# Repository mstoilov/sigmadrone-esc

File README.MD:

This is the sigmadrone ESC repository. It contains hardware designs and
firmware software for the Sigmadrone ESC.

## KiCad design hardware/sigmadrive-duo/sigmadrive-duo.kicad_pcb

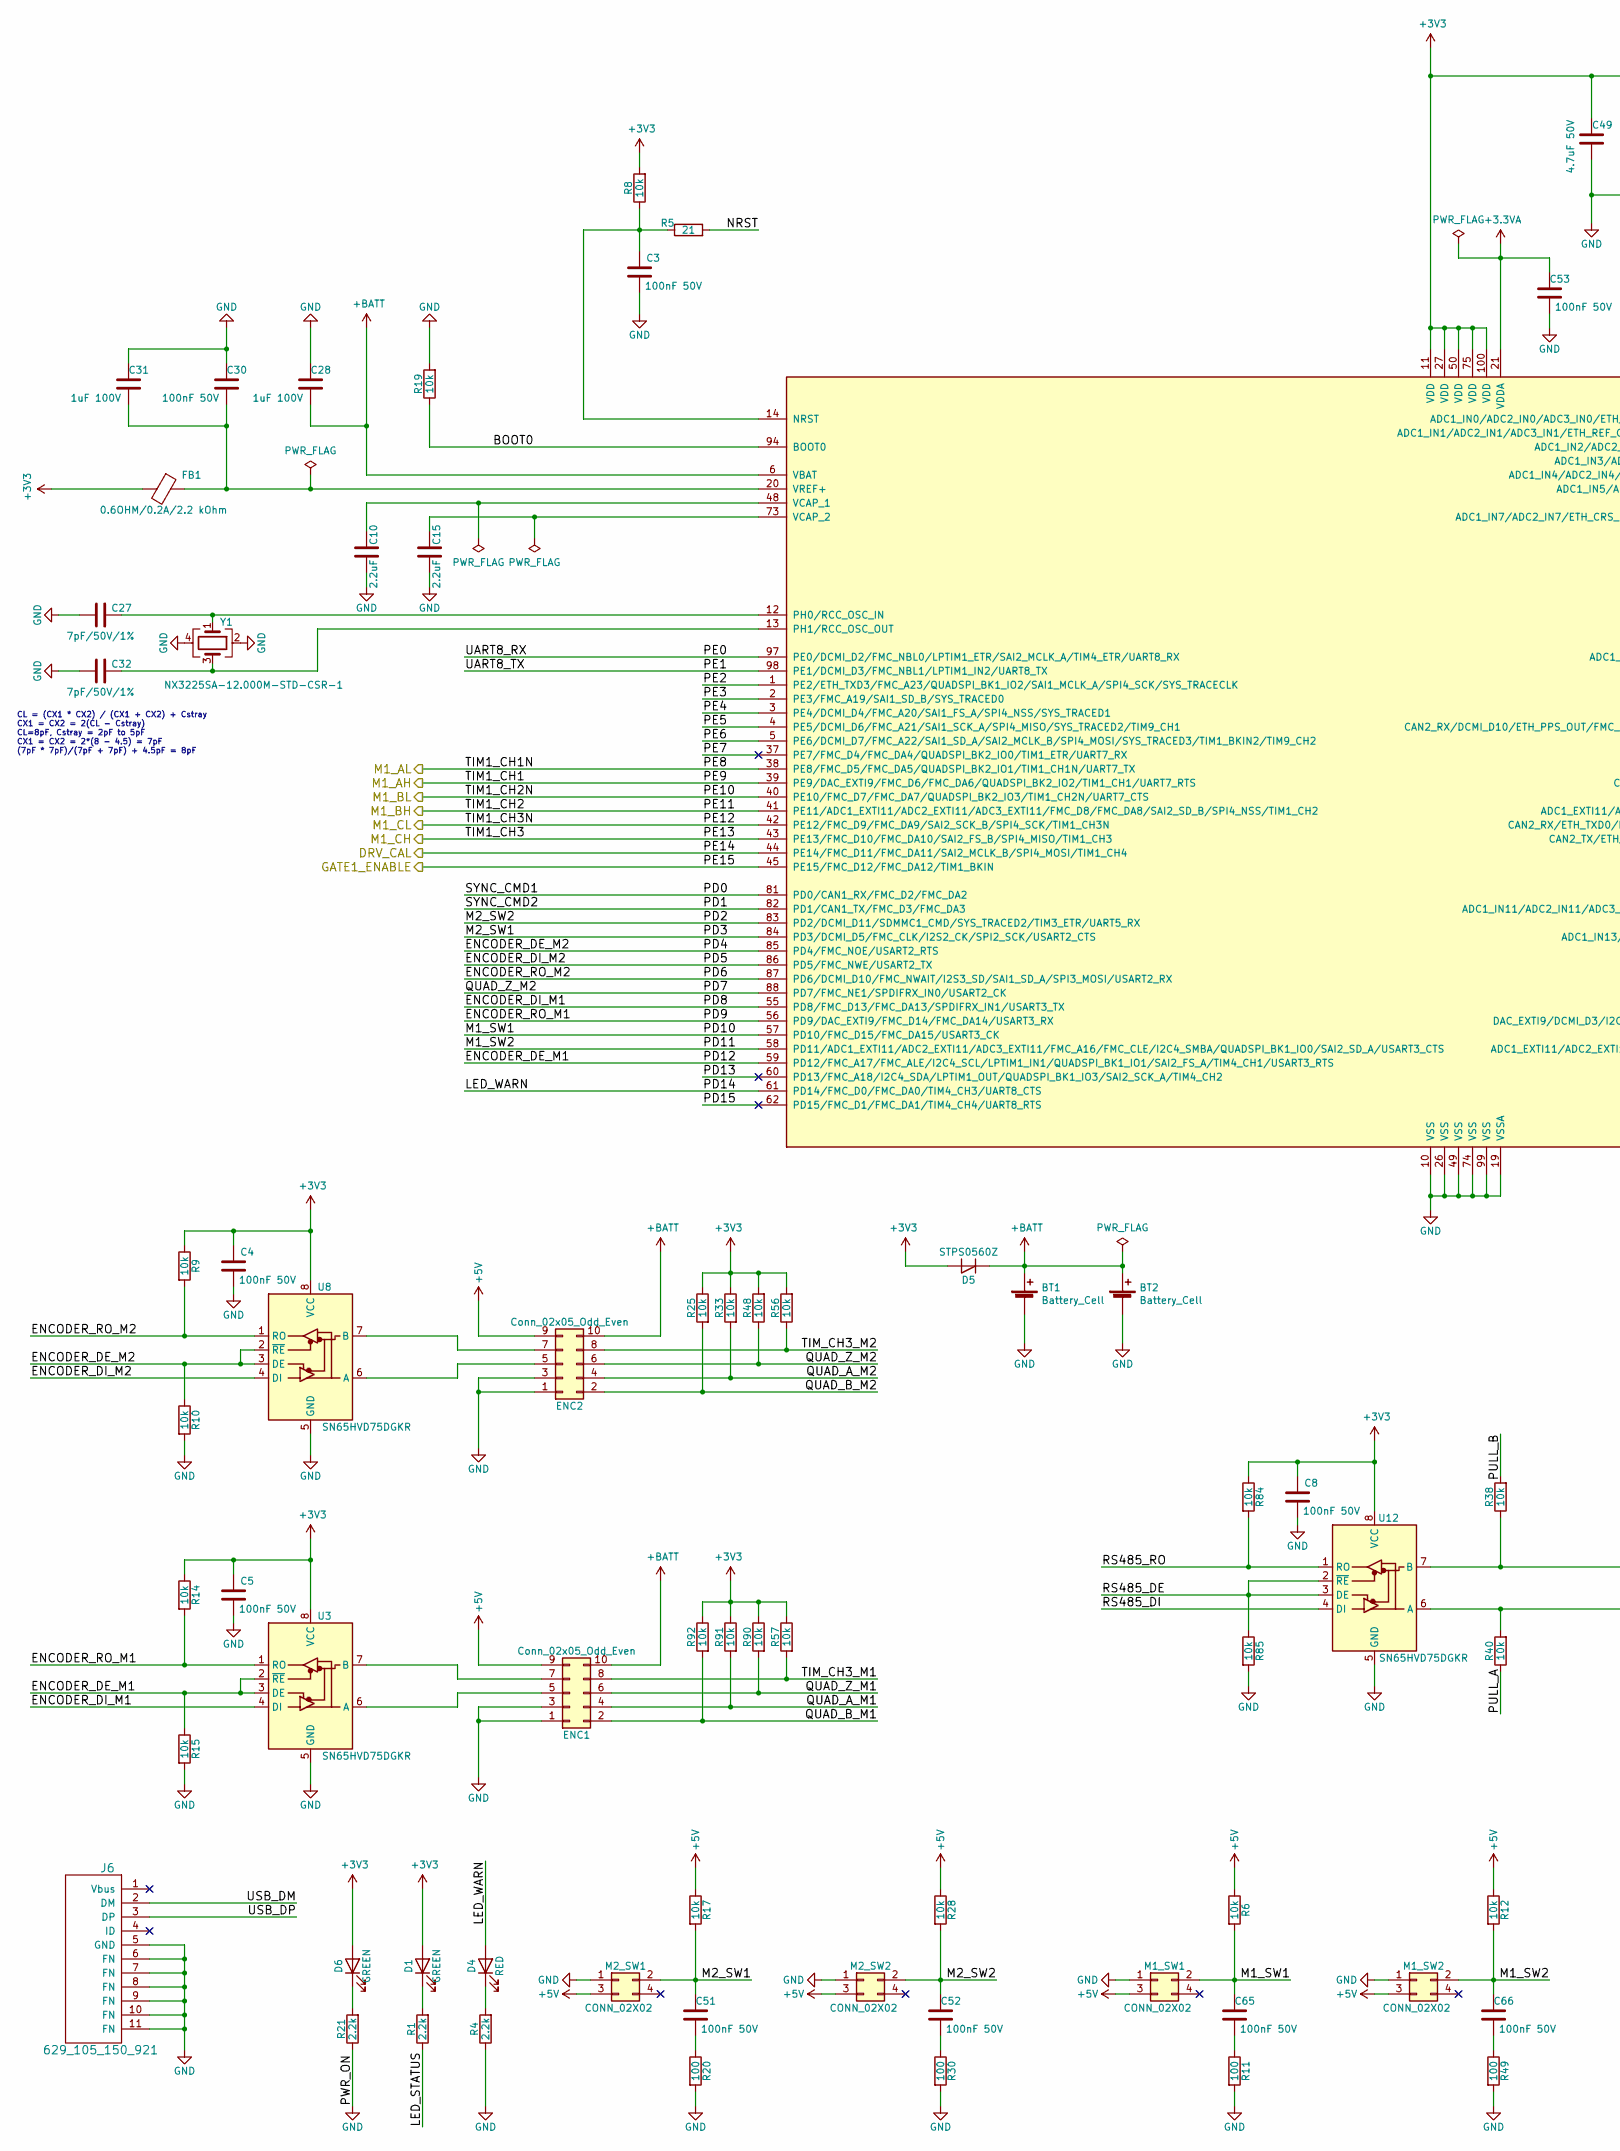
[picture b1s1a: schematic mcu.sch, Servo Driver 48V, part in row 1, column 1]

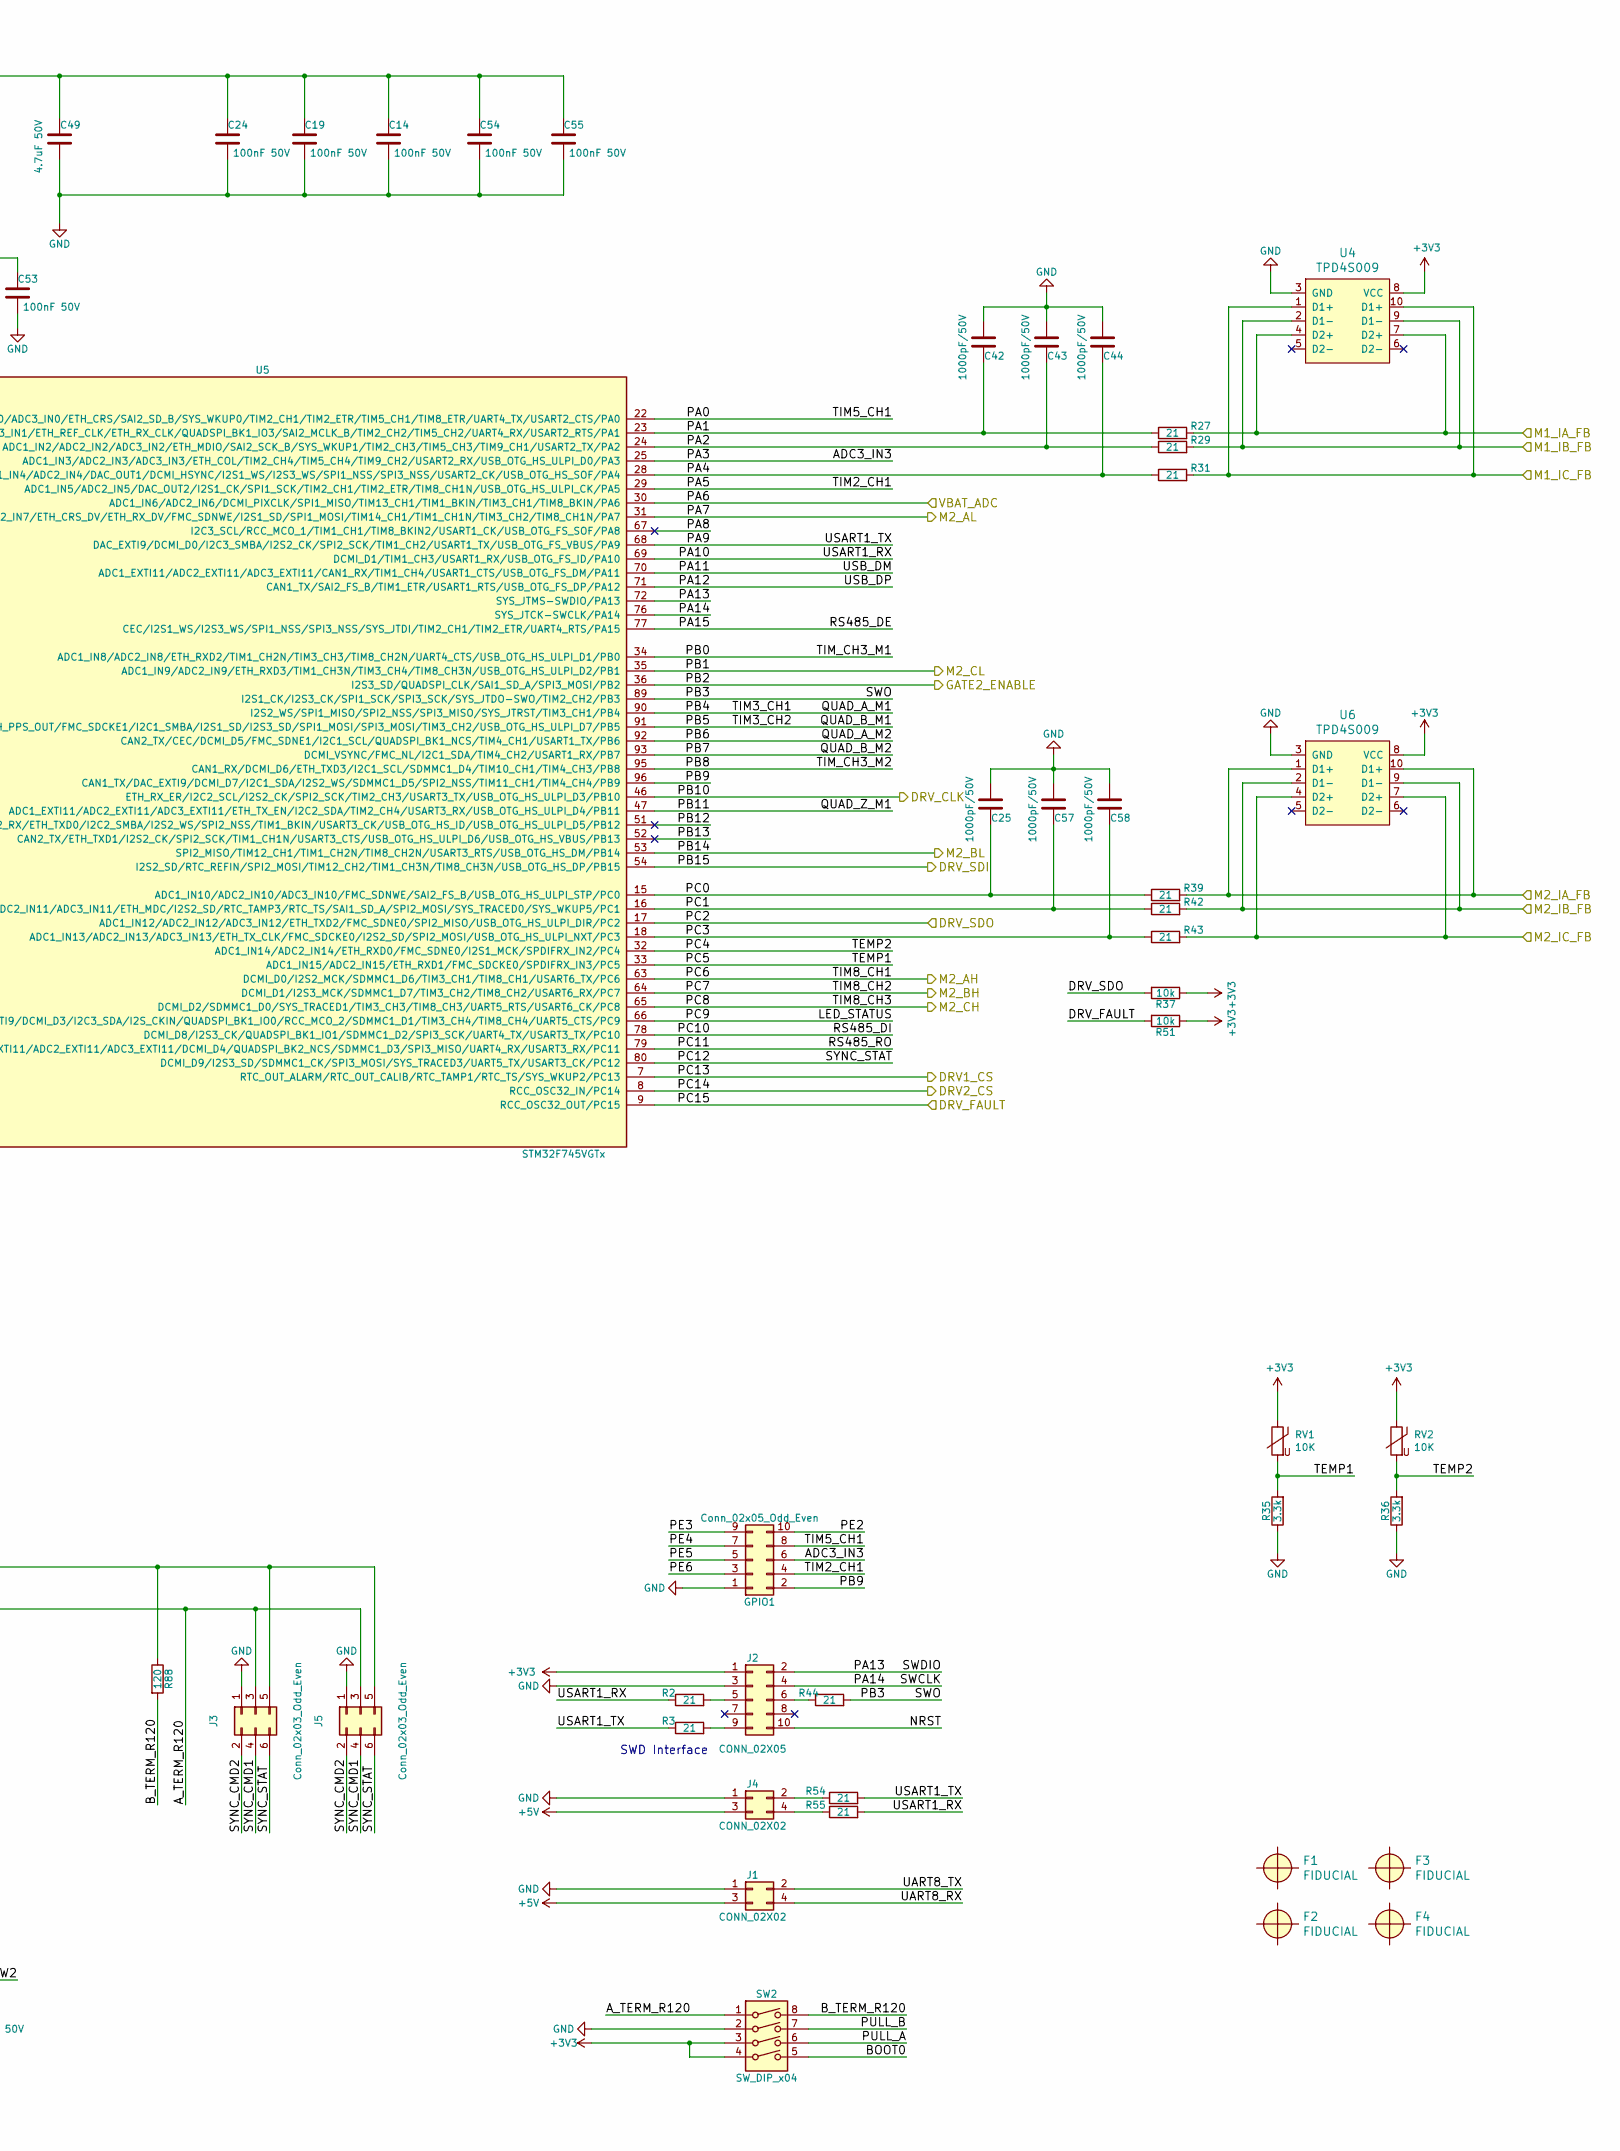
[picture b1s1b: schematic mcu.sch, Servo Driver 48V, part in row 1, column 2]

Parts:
BT1, BT2: Battery_Cell; Battery_Panasonic_CR1220-VCN_Vertical_CircularHoles; Part VL-1220/VCN
C3, C4, C5, C8, C14, C19, C24, C30, C51, C52, C53, C54, C55, C65, C66: 100nF 50V; C_0603_1608Metric; Part 490-4779-2-ND
C10, C15: 2.2uF; C_0603_1608Metric; Part 490-10731-1-ND
C25, C42, C43, C44, C57, C58: 1000pF/50V; C_0603_1608Metric; Part 1276-1091-2-ND
C27, C32: 7pF/50V/1%; C_0603_1608Metric; Part ‎1276-2137-1-ND‎
C28, C31: 1uF 100V; C_0805_2012Metric; Part 445-6804-2-ND
C49: 4.7uF 50V; C_0805_2012Metric; Part 490-10751-2-ND
D1, D6: GREEN; LED_0603_1608Metric; Part 732-4971-1-ND
D4: RED; LED_0603_1608Metric; Part 732-4978-1-ND
D5: STPS0560Z; D_SOD-123; Part 497-3787-1-ND
ENC1, ENC2: Conn_02x05_Odd_Even; PinHeader_2x05_P2.00mm_Horizontal; Part H10247-ND
F1, F2, F3, F4: FIDUCIAL; Fiducial_0.5mm_Dia_1mm_Outer
FB1: 0.6OHM/0.2A/2.2 kOhm; R_0603_1608Metric; Part 732-1609-1-ND
GPIO1: Conn_02x05_Odd_Even; PinHeader_2x05_P2.00mm_Horizontal
J1, J4: CONN_02X02; PinHeader_2x02_P2.00mm_Horizontal; Part 732-5374-ND
J2: CONN_02X05; PinHeader_2x05_P1.27mm_Vertical; Part 732-5374-ND
J3, J5: Conn_02x03_Odd_Even; PinHeader_2x03_P2.00mm_Horizontal; Part H2866-ND
J6: 629_105_150_921; WURTH_629105150921_NO_OVALS; Part 732-5961-1-ND
M1_SW1, M1_SW2, M2_SW1, M2_SW2: CONN_02X02; PinHeader_2x02_P2.00mm_Horizontal; Part H10244-ND
R1, R4, R21: 2.2k; R_0603_1608Metric; Part RMCF0603JT2K20CT-ND
R2, R3, R5, R27, R29, R31, R39, R42, R43, R44, R54, R55: 21; R_0603_1608Metric; Part 311-21.0HRCT-ND
R6, R8, R9, R10, R12, R14, R15, R17, R19, R25, R28, R33, R37, R38, R40, R48, R51, R56, R57, R84, R85, R90, R91, R92: 10k; R_0603_1608Metric; Part 311-10.0KHRCT-ND
R11, R20, R30, R49: 100; R_0603_1608Metric; Part 311-100HRCT-ND
R35, R36: 3.3k; R_0603_1608Metric; Part 311-3.30KHRCT-ND
R88: 120; R_0603_1608Metric; Part 311-100HRCT-ND
RV1, RV2: 10K; R_0603_1608Metric; Part P12014CT-ND
SW2: SW_DIP_x04; SW_DIP_SPSTx04_Slide_Copal_CHS-04A_W5.08mm_P1.27mm_JPin; Part GH7644CT-ND
U3, U8, U12: SN65HVD75DGKR; SOIC-8_3.9x4.9mm_P1.27mm; Part 296-35070-1-ND
U4, U6: TPD4S009; TSSOP-10_3x3mm_P0.5mm; Part 296-24538-1-ND
U5: STM32F745VGTx; LQFP-100_14x14mm_P0.5mm; Part 497-16605-ND
Y1: NX3225SA-12.000M-STD-CSR-1; Crystal_SMD_3225-4Pin_3.2x2.5mm; Part 644-1047-1-ND

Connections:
+3.3VA: C53.2, U5.21 (VDDA); also elsewhere on the board
+5V: ENC1.9, ENC2.9, J1.3, J4.3, M1_SW1.3, M1_SW2.3, M2_SW1.3, M2_SW2.3, R6.1, R12.1, R17.1, R28.1; also elsewhere on the board
+BATT: BT1.1 (+), BT2.1 (+), C28.1, D5.1 (K), ENC1.10, ENC2.10, U5.6 (VBAT)
/MCU/ADC3_IN3: GPIO1.6, U5.25 (ADC1_IN3/ADC2_IN3/ADC3_IN3/ETH_COL/TIM2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)
/MCU/A_TERM_R120: J3.3, J5.3, R40.2, SW2.1, U12.6 (A)
/MCU/BOOT0: R19.1, SW2.5, U5.94 (BOOT0)
/MCU/B_TERM_R120: R88.2, SW2.8
/MCU/DRV1_CS: U5.7 (RTC_OUT_ALARM/RTC_OUT_CALIB/RTC_TAMP1/R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); also elsewhere on the board
/MCU/DRV2_CS: U5.8 (RCC_OSC32_IN/PC14); also elsewhere on the board
/MCU/DRV_CAL: U5.44 (PE14/FMC_D11/FMC_DA11/SAI2_MCLK_B/SPI4_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); also elsewhere on the board
/MCU/DRV_CLK: U5.46 (ETH_RX_ER/I2C2_SCL/I2S2_CK/SPI2_SCK/TIM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); also elsewhere on the board
/MCU/DRV_FAULT: R51.2, U5.9 (RCC_OSC32_OUT/PC15); also elsewhere on the board
/MCU/DRV_SDI: U5.54 (I2S2_SD/RTC_REFIN/SPI2_MOSI/TIM12_CH2/T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); also elsewhere on the board
/MCU/DRV_SDO: R37.2, U5.17 (ADC1_IN12/ADC2_IN12/ADC3_IN12/ETH_TXD2/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); also elsewhere on the board
/MCU/ENCODER_DE_M1: R15.1, U3.2 (~RE), U3.3 (DE), U5.59 (PD12/FMC_A17/FMC_ALE/I2C4_SCL/LPTIM1_IN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)
/MCU/ENCODER_DE_M2: R10.1, U5.85 (PD4/FMC_NOE/USART2_RTS), U8.2 (~RE), U8.3 (DE)
/MCU/ENCODER_DI_M1: U3.4 (DI), U5.55 (PD8/FMC_D13/FMC_DA13/SPDIFRX_IN1/USART3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)
/MCU/ENCODER_DI_M2: U5.86 (PD5/FMC_NWE/USART2_TX), U8.4 (DI)
/MCU/ENCODER_RO_M1: R14.2, U3.1 (RO), U5.56 (PD9/DAC_EXTI9/FMC_D14/FMC_DA14/USART3_RX)
/MCU/ENCODER_RO_M2: R9.2, U5.87 (PD6/DCMI_D10/FMC_NWAIT/I2S3_SD/SAI1_SD_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), U8.1 (RO)
/MCU/GATE1_ENABLE: U5.45 (PE15/FMC_D12/FMC_DA12/TIM1_BKIN); also elsewhere on the board
/MCU/GATE2_ENABLE: U5.36 (I2S3_SD/QUADSPI_CLK/SAI1_SD_A/SPI3_MOSI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); also elsewhere on the board
/MCU/LED_STATUS: R1.1, U5.66 (DAC_EXTI9/DCMI_D3/I2C3_SDA/I2S_CKIN/QUA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)
/MCU/LED_WARN: D4.2 (A), U5.61 (PD14/FMC_D0/FMC_DA0/TIM4_CH3/UART8_CTS)
/MCU/M1_AH: U5.39 (PE9/DAC_EXTI9/FMC_D6/FMC_DA6/QUADSPI_BK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); also elsewhere on the board
/MCU/M1_AL: U5.38 (PE8/FMC_D5/FMC_DA5/QUADSPI_BK2_IO1/TIM1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); also elsewhere on the board
/MCU/M1_BH: U5.41 (PE11/ADC1_EXTI11/ADC2_EXTI11/ADC3_EXTI1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); also elsewhere on the board
/MCU/M1_BL: U5.40 (PE10/FMC_D7/FMC_DA7/QUADSPI_BK2_IO3/TIM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); also elsewhere on the board
/MCU/M1_CH: U5.43 (PE13/FMC_D10/FMC_DA10/SAI2_FS_B/SPI4_MI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); also elsewhere on the board
/MCU/M1_CL: U5.42 (PE12/FMC_D9/FMC_DA9/SAI2_SCK_B/SPI4_SCK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); also elsewhere on the board
/MCU/M1_IA_FB: R27.2, U4.4 (D2+), U4.7 (D2+); also elsewhere on the board
/MCU/M1_IB_FB: R29.2, U4.2 (D1-), U4.9 (D1-); also elsewhere on the board
/MCU/M1_IC_FB: R31.2, U4.1 (D1+), U4.10 (D1+); also elsewhere on the board
/MCU/M1_SW1: C65.2, M1_SW1.2, R6.2, U5.57 (PD10/FMC_D15/FMC_DA15/USART3_CK)
/MCU/M1_SW2: C66.2, M1_SW2.2, R12.2, U5.58 (PD11/ADC1_EXTI11/ADC2_EXTI11/ADC3_EXTI1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)
/MCU/M2_AH: U5.63 (DCMI_D0/I2S2_MCK/SDMMC1_D6/TIM3_CH1/TIM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); also elsewhere on the board
/MCU/M2_AL: U5.31 (ADC1_IN7/ADC2_IN7/ETH_CRS_DV/ETH_RX_DV/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); also elsewhere on the board
/MCU/M2_BH: U5.64 (DCMI_D1/I2S3_MCK/SDMMC1_D7/TIM3_CH2/TIM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); also elsewhere on the board
/MCU/M2_BL: U5.53 (SPI2_MISO/TIM12_CH1/TIM1_CH2N/TIM8_CH2N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); also elsewhere on the board
/MCU/M2_CH: U5.65 (DCMI_D2/SDMMC1_D0/SYS_TRACED1/TIM3_CH3/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); also elsewhere on the board
/MCU/M2_CL: U5.35 (ADC1_IN9/ADC2_IN9/ETH_RXD3/TIM1_CH3N/TI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); also elsewhere on the board
/MCU/M2_IA_FB: R39.2, U6.1 (D1+), U6.10 (D1+); also elsewhere on the board
/MCU/M2_IB_FB: R42.2, U6.2 (D1-), U6.9 (D1-); also elsewhere on the board
/MCU/M2_IC_FB: R43.2, U6.4 (D2+), U6.7 (D2+); also elsewhere on the board
/MCU/M2_SW1: C51.2, M2_SW1.2, R17.2, U5.84 (PD3/DCMI_D5/FMC_CLK/I2S2_CK/SPI2_SCK/US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)
/MCU/M2_SW2: C52.2, M2_SW2.2, R28.2, U5.83 (PD2/DCMI_D11/SDMMC1_CMD/SYS_TRACED2/TIM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)
/MCU/NRST: J2.10, R5.2
/MCU/PA0: GPIO1.8, U5.22 (ADC1_IN0/ADC2_IN0/ADC3_IN0/ETH_CRS/SAI2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)
/MCU/PA1: C42.1, R27.1, U5.23 (ADC1_IN1/ADC2_IN1/ADC3_IN1/ETH_REF_CLK/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)
/MCU/PA2: C43.1, R29.1, U5.24 (ADC1_IN2/ADC2_IN2/ADC3_IN2/ETH_MDIO/SAI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)
/MCU/PA4: C44.1, R31.1, U5.28 (ADC1_IN4/ADC2_IN4/DAC_OUT1/DCMI_HSYNC/I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)
/MCU/PA5: GPIO1.4, U5.29 (ADC1_IN5/ADC2_IN5/DAC_OUT2/I2S1_CK/SPI1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)
/MCU/PA8: U5.67 (I2C3_SCL/RCC_MCO_1/TIM1_CH1/TIM8_BKIN2/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)
/MCU/PA9: R3.1, R54.2, U5.68 (DAC_EXTI9/DCMI_D0/I2C3_SMBA/I2S2_CK/SPI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)
/MCU/PA10: R2.1, R55.2, U5.69 (DCMI_D1/TIM1_CH3/USART1_RX/USB_OTG_FS_I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)
/MCU/PA11: J6.2 (DM), U5.70 (ADC1_EXTI11/ADC2_EXTI11/ADC3_EXTI11/CAN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)
/MCU/PA12: J6.3 (DP), U5.71 (CAN1_TX/SAI2_FS_B/TIM1_ETR/USART1_RTS/U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)
/MCU/PA13: J2.2, U5.72 (SYS_JTMS-SWDIO/PA13)
/MCU/PA14: J2.4, U5.76 (SYS_JTCK-SWCLK/PA14)
/MCU/PA15: R85.1, U5.77 (CEC/I2S1_WS/I2S3_WS/SPI1_NSS/SPI3_NSS/S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), U12.2 (~RE), U12.3 (DE)
/MCU/PB0: ENC1.8, R57.2, U5.34 (ADC1_IN8/ADC2_IN8/ETH_RXD2/TIM1_CH2N/TI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)
/MCU/PB3: R44.2, U5.89 (I2S1_CK/I2S3_CK/SPI1_SCK/SPI3_SCK/SYS_J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)
/MCU/PB4: ENC1.4, R91.2, U5.90 (I2S2_WS/SPI1_MISO/SPI2_NSS/SPI3_MISO/SY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)
/MCU/PB5: ENC1.2, R92.2, U5.91 (CAN2_RX/DCMI_D10/ETH_PPS_OUT/FMC_SDCKE1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)
/MCU/PB6: ENC2.4, R33.2, U5.92 (CAN2_TX/CEC/DCMI_D5/FMC_SDNE1/I2C1_SCL/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)
/MCU/PB7: ENC2.2, R25.2, U5.93 (DCMI_VSYNC/FMC_NL/I2C1_SDA/TIM4_CH2/USA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)
/MCU/PB8: ENC2.8, R56.1, U5.95 (CAN1_RX/DCMI_D6/ETH_TXD3/I2C1_SCL/SDMMC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)
/MCU/PB9: GPIO1.2, U5.96 (CAN1_TX/DAC_EXTI9/DCMI_D7/I2C1_SDA/I2S2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)
/MCU/PB11: ENC1.6, R90.2, U5.47 (ADC1_EXTI11/ADC2_EXTI11/ADC3_EXTI11/ETH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)
/MCU/PB12: U5.51 (CAN2_RX/ETH_TXD0/I2C2_SMBA/I2S2_WS/SPI2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)
/MCU/PB13: U5.52 (CAN2_TX/ETH_TXD1/I2S2_CK/SPI2_SCK/TIM1_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)
/MCU/PC0: C25.1, R39.1, U5.15 (ADC1_IN10/ADC2_IN10/ADC3_IN10/FMC_SDNWE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)
/MCU/PC1: C57.1, R42.1, U5.16 (ADC1_IN11/ADC2_IN11/ADC3_IN11/ETH_MDC/I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)
/MCU/PC3: C58.1, R43.1, U5.18 (ADC1_IN13/ADC2_IN13/ADC3_IN13/ETH_TX_CL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)
/MCU/PC4: R36.2, RV2.2, U5.32 (ADC1_IN14/ADC2_IN14/ETH_RXD0/FMC_SDNE0/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)
/MCU/PC5: R35.2, RV1.2, U5.33 (ADC1_IN15/ADC2_IN15/ETH_RXD1/FMC_SDCKE0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)
/MCU/PC10: U5.78 (DCMI_D8/I2S3_CK/QUADSPI_BK1_IO1/SDMMC1_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), U12.4 (DI)
/MCU/PC11: R84.2, U5.79 (ADC1_EXTI11/ADC2_EXTI11/ADC3_EXTI11/DCM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), U12.1 (RO)
/MCU/PC12: J3.6, J5.6, U5.80 (DCMI_D9/I2S3_SD/SDMMC1_CK/SPI3_MOSI/SYS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)
/MCU/PD0: J3.4, J5.4, U5.81 (PD0/CAN1_RX/FMC_D2/FMC_DA2)
/MCU/PD1: J3.2, J5.2, U5.82 (PD1/CAN1_TX/FMC_D3/FMC_DA3)
/MCU/PD7: ENC2.6, R48.1, U5.88 (PD7/FMC_NE1/SPDIFRX_IN0/USART2_CK)
/MCU/PD13: U5.60 (PD13/FMC_A18/I2C4_SDA/LPTIM1_OUT/QUADSP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)
/MCU/PD15: U5.62 (PD15/FMC_D1/FMC_DA1/TIM4_CH4/UART8_RTS)
/MCU/PE0: J1.4, U5.97 (PE0/DCMI_D2/FMC_NBL0/LPTIM1_ETR/SAI2_MC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)
/MCU/PE1: J1.2, U5.98 (PE1/DCMI_D3/FMC_NBL1/LPTIM1_IN2/UART8_TX)
/MCU/PE2: GPIO1.10, U5.1 (PE2/ETH_TXD3/FMC_A23/QUADSPI_BK1_IO2/SA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)
/MCU/PE3: GPIO1.9, U5.2 (PE3/FMC_A19/SAI1_SD_B/SYS_TRACED0)
/MCU/PE4: GPIO1.7, U5.3 (PE4/DCMI_D4/FMC_A20/SAI1_FS_A/SPI4_NSS/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)
/MCU/PE5: GPIO1.5, U5.4 (PE5/DCMI_D6/FMC_A21/SAI1_SCK_A/SPI4_MIS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)
/MCU/PE6: GPIO1.3, U5.5 (PE6/DCMI_D7/FMC_A22/SAI1_SD_A/SAI2_MCLK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)
/MCU/PE7: U5.37 (PE7/FMC_D4/FMC_DA4/QUADSPI_BK2_IO0/TIM1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)
/MCU/PULL_A: R40.1, SW2.6
/MCU/PULL_B: R38.2, SW2.7
/MCU/VBAT_ADC: U5.30 (ADC1_IN6/ADC2_IN6/DCMI_PIXCLK/SPI1_MISO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); also elsewhere on the board
GND: BT1.2 (-), BT2.2 (-), C3.1, C4.1, C5.1, C8.1, C10.1, C14.1, C15.1, C19.1, C24.1, C25.2, C27.2, C28.2, C30.2, C31.2, C32.2, C42.2, C43.2, C44.2, C49.2, C53.1, C54.1, C55.1, C57.2, C58.2, ENC1.1, ENC1.3, ENC2.1, ENC2.3, GPIO1.1, J1.1, J2.3, J3.1, J4.1, J5.1, J6.5 (GND), J6.6 (FN), J6.7 (FN), J6.8 (FN), J6.9 (FN), J6.10 (FN), J6.11 (FN), M1_SW1.1, M1_SW2.1, M2_SW1.1, M2_SW2.1, R4.1, R10.2, R11.2, R15.2, R19.2, R20.2, R21.1, R30.2, R35.1, R36.1, R49.2, R85.2, SW2.2, U3.5 (GND), U4.3 (GND), U5.10 (VSS), U5.19 (VSSA), U5.26 (VSS), U5.49 (VSS), U5.74 (VSS), U5.99 (VSS), U6.3 (GND), U8.5 (GND), U12.5 (GND), Y1.2, Y1.4; also elsewhere on the board
unnamed: C3.2, R5.1, R8.1, U5.14 (NRST)
unnamed: C10.2, U5.48 (VCAP_1)
unnamed: C15.2, U5.73 (VCAP_2)
unnamed: C27.1, U5.12 (PH0/RCC_OSC_IN), Y1.1
unnamed: C30.1, C31.1, FB1.1, U5.20 (VREF+)
unnamed: C32.1, U5.13 (PH1/RCC_OSC_OUT), Y1.3
unnamed: C51.1, R20.1
unnamed: C52.1, R30.1
unnamed: C65.1, R11.1
unnamed: C66.1, R49.1
unnamed: D1.1 (K), R1.2
unnamed: D4.1 (K), R4.2
unnamed: D6.1 (K), R21.2
unnamed: ENC1.5, U3.6 (A)
unnamed: ENC1.7, U3.7 (B)
unnamed: ENC2.5, U8.6 (A)
unnamed: ENC2.7, U8.7 (B)
unnamed: J2.5, R2.2
unnamed: J2.6, R44.1
unnamed: J2.9, R3.2
unnamed: J3.5, J5.5, R38.1, R88.1, U12.7 (B)
unnamed: J4.2, R54.1
unnamed: J4.4, R55.1

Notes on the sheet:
SWD Interface
CL = (CX1 * CX2) / (CX1 + CX2) + Cstray CX1 = CX2 = 2(CL - Cstray) CL=8pF, Cstray = 2pF to 5pF CX1 = CX2 = 2*(8 - 4.5) = 7pF (7pF * 7pF)/(7pF + 7pF) + 4.5pF = 8pF

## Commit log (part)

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2019-10-30 work on properties.
2019-10-30 Updated to_string() to support array and object.
2019-10-31 Added Panasonic connection info.
2019-10-31 Changed the MCU to STM32F745VG
2019-11-13 Added Adc regular channel conversions.
2019-11-14 Added worker thread in CdcIface
2019-11-14 Added worker thread in CdcIface 2
2019-11-15 Work on ADC measurements. 2
2019-11-15 Work on ADC measurements. 3
2019-11-16 Added TIM2 trigger for the ADC1 regular channels.
2019-11-16 Set the ADC trigger to ADC_EXTERNALTRIGINJECCONV_T1_TRGO
2019-11-16 Remove the TIM2 timer from CubeMX configuration.
2019-11-16 Set TIM1_RCR=5
2019-11-17 Removed the TIM1 Update interrupt.
2019-11-21 Implementation of using complex numbers to track rotor and current.
2019-11-22 Enabled FreeRTOS allocated _reent context for every task.
2019-11-22 Work on using complex numbers for Rotor/Current tracking.
2019-11-24 Added scheduler class
2019-11-24 Work on scheduler
2019-11-24 Work on scheduler, now using CMSIS v1
2019-11-25 Work on scheduler using CMSIS v2 - 2
2019-11-25 Work on scheduler using CMSIS v2 - 3
2019-11-25 Added IsDispatching() method.
2019-11-25 Added task rotation task.
2019-11-28 Added support for rpc_wrapper
2019-11-28 Use update_counter_
2019-11-28 Make the RpcServer global. Using rexjson::make_rpc_wrapper to expose ServoDrive::Start ServoDrive::Stop with RPC.
2019-11-29 Removed unused ...AArgs typename
2019-11-29 Work on resistance measurement.
2019-11-30 Added ApplyPhaseVoltage()
2019-11-30 Fixed type detection.
2019-11-30 Start with gain set to 10VV
2019-11-30 Cleaned up the PwmGenerator.
2019-12-01 Work on inductance measurement.
2019-12-04 Added encoder_dir_ detection task.
2019-12-04 Changed the SVM to be within 0 to 1.0
2019-12-05 Added task for index search
2019-12-05 Restored IRQ priority back to 5
2019-12-05 Work on rotor reset.
2019-12-05 Created Config structure to hold all ServoDrive configuration data.
2019-12-07 ServoDrive clean up.
2019-12-07 Clean up - removed unused code.
2019-12-07 Removed unused RPC functions.
2019-12-10 Removed iservodrive.h/cpp files.
2019-12-10 Renamed servo_drive.h/cpp to motor_drive.h/cpp
2019-12-10 Renamed motor_drive.h/cpp to motordrive.h/cpp
2019-12-12 Added support for space separated command and parameters.
2019-12-12 Added DumpDebugData()
2019-12-13 Added Minas A4 encoder.
2019-12-13 work on panasonic encoder.
2019-12-15 Fixed osEventFlagsSet fails with called from ISR https://github.com/ARM-software/CMSIS-FreeRTOS/issues/12
2019-12-15 Added files hrtimer.h/cpp
2019-12-15 Added High Resolution Timer.
2019-12-18 Added support to externally set the active encoder.
2019-12-18 Moved the encoder_->Update() call inside the scheduler thread.
2019-12-19 Added encoder UpdateBegin()/UpdateEnd()
2019-12-19 Added DCache support.
2019-12-19 Added support for dcache memory management.
2019-12-21 Added DCache management in the USB interface.
2019-12-21 Added emergency stop for all motors.
2019-12-23 Removed mutex synchronization.
2019-12-23 Set the TIM1 period to 4500 clock cycles.
2019-12-26 Work on FOC
2019-12-28 Work on speed loop
2019-12-29 Work on FOC torque/speed
2019-12-30 Work on FOC velocity/torque control.
2019-12-31 Added spin task in FOC.
2020-01-01 Avoid using std::polar<float>().
2020-01-01 Added support for synchronous transmit in the CDC interface.
2020-01-02 Display encoder timings.
2020-01-03 Moved rotor update out of the MotorDrive.
2020-01-03 RCR 0. Fixed minas encoder ResetPosition()
2020-01-04 Set max calibration current to 4.
2020-01-04 Code clean-up.
2020-01-05 Work no velocity loop.
2020-01-05 Reduced SPI speed.
2020-01-06 Added Idq filters.
2020-01-07 Fixed exponential number parsing in the rexcc file.
2020-01-07 Added support for configuration saving in flash memory.
2020-01-08 Fixed encoder detection.
2020-01-10 Work on position loop.
2020-01-11 Moved the RPC server code to rexjsonrpc directory.
2020-01-11 Fixed int64 property.
2020-01-13 Added support for RS485 comunication.
2020-01-21 Initial check-in of the sigmadrive-tool.
2020-01-21 Work on RS485 communication.
2020-01-23 Added better error reporting for the rexjson parser.
2020-01-25 Commented out debug messages.
2020-01-27 temp save.
2020-01-31 code cleanup for appmain.cpp
2020-02-01 Fixed #include to also have the containing directory.
2020-02-01 Moved driver 8323 default init in a separate method.
2020-02-02 Work on iencoder interface.
2020-02-02 Fixed rexjson::value constructors.
2020-02-02 removed casting.
2020-04-07 Testing auto doc.
2020-04-07 Added blinkled class.
2020-04-07 Work on encoder interface. Added dumbencoder.h
2020-05-07 Documented the PidController.
2020-05-07 work on MotorDrive documentation.
2020-05-07 Added delay before attempting to initialize the encoder.
2020-05-08 Added AdcData class. Added more documentation.
2020-05-09 Use spaces for indentation.
2020-05-09 Commented the pwm generator.
2020-05-09 Added more documentation for the MotorDrive class
2020-05-10 Simplified the IEncoder interface.
2020-05-12 Work on speed control.
2020-05-12 Removed usage of crossE
2020-05-13 Work on documentation.
2020-05-13 Fixed doc error
2020-05-13 Changed default values for resistance and inductance
2020-05-14 Changed default gains for the PID regulators.
2020-05-14 Use ADC2 and ADC3 for current sensing.
2020-05-14 Use position loop that generates velocity.
2020-05-24 work on position loop
2020-05-24 renamed PidController input param to error.
2020-05-25 work on PID controller.
2020-05-25 Implemented anti-windup dynamic clamping for the PID
2020-05-25 Debug uart output
2020-07-14 Enabled automatic PID calibration.
2020-07-16 Fixed encoder dir detection. Tuned the current control loop.
2020-07-17 Changed SetEncoder to accept desired encoder resolution bits.
2020-07-28 Updated PID controller parameters
2020-07-31 added velocity profiler.
2020-08-02 Fixed velocity profiler.
2020-08-07 Fixed build for the stand alone build.
2020-08-09 Work on duo drive.
2020-08-14 Sigmadrive-duo final HW update
2020-08-15 removed lpf_Aenc_
2020-08-15 Added sigmadrive-duo.ioc
2020-08-16 removed mechanical angle calculation.
2020-08-16 Changed the Wenc to be encoder counts per update period
2020-08-16 Removed enc_update_period
2020-08-16 Updated speed PID coefficients.
2020-08-16 Removed phase current filters.
2020-08-17 Removed current filters.
2020-08-17 sync TIM1 and TIM8
2020-08-18 Work on adding support for second axis.
2020-08-19 syncing TIM1 and TIM8
2020-08-19 Updated STM32CubeMX
2020-08-19 Work on supporting two axes
2020-08-19 updated STM32CubeMX files.
2020-08-20 Work on dual motor support.
2020-08-20 updated ld script
2020-08-20 Renamed PidController to PIDController
2020-08-20 removed SampledData structure.
2020-08-20 Set up the dumb encoder.
2020-08-21 Optimized the TrapezoidalProfile data calculations.
2020-08-21 Updated ModeClosedLoopTrajectory
2020-08-22 Added Anti-windup dynamic clamping of the integral component in the PI controller.
2020-08-22 Fixed ModeClosedLoopTrajectory initialization. Updated PID coefficients.
2020-08-25 Updated max allowed values.
2020-08-26 Move the encoder debug functionality to the MinasA4Encoder class.
2020-08-26 Added support for rading two encoders.
2020-08-27 Added RPC interface to the MA4 encoder.
2020-08-27 Stopped using HAL_UART APIs.
2020-08-28 Reworked minas encoder driver.
2020-08-28 Using DSP math functions.
2020-08-28 Introduced enc_position_size_half_ member varialbe.
2020-08-29 Added profiler using int arithmetic.
2020-08-29 Added Hz param to TrapezoidalProfile::Init
2020-08-29 Disabled encoder CRC calculation. Added PREFETCH_ENABLE
2020-08-29 Added void EstimateRotor(); and Rencest_ to support rotor position estimation.
2020-09-01 Initial support for DUO.
2020-09-01 Fixed SPI communication with DRV8323
2020-09-02 added dma_adc pointer.
2020-09-02 Added Voltage reading for axis2.
2020-09-03 Work on DUO support.
2020-09-04 PCB sigmadrive-duo, version 3.6
2020-09-04 Added RPC variable Rencest_
2020-09-05 Added functions to move both axes together.
2020-09-08 Changed the values of the gate drive currents.
2020-09-09 Work on velocity streaming.
2020-09-11 Added four point trapezoidal profile generation.
2020-09-15 Hardware version 3.8. Adde support for external battery.
2020-09-22 Added PQFN_5x6_SGD and molex connector models.
2020-10-01 Changed the SPI2 baud rate to 843 KB/s
2020-10-02 Make UART_IT_IDLE optional
2020-10-02 Added UART4 global interrupt.
2020-10-02 Added UART4 to be used with RPC Task
2020-12-28 Fix RunRpcTask.
2021-02-14 Switch TIM1 and TIM8, so they control TIM1 -> M1, TIM8 -> M2
2021-02-14 save settings
2021-02-14 removed rexjson Makefile
2021-02-19 Removed unused RPC methods
2021-07-18 Changed Documentation string.
2021-07-18 Removed file torque_loop.h/cpp
2021-10-12 Added config propertis that can be stored to the FLASH.
2022-10-13 Updated firmware. Changes have been sitting on my computer for long time.
2022-10-13 How to setup the ttyACM0 comment.
2022-11-28 check in ryno cst dirs
2022-11-28 Added .vscode dir
2022-11-28 Added ryno to the makefile
2022-11-30 Added RunRynoCommandTask
2022-11-30 removed rexjson from the project. added ryno script engine.
2022-12-10 commit settings, launch files.
2022-12-13 Added motorctrlobject.h/cpp files.
2022-12-13 Added MotorctrlObject
2022-12-15 Added motor FOC properties to ryno scripting environment.
2022-12-15 Set the font size to 16
2022-12-15 Added the encoder specs.
2022-12-15 Removed unused variable: max_poserr_factor_
2022-12-16 Fixed the build for mac.
2022-12-17 Code clean up. Removed unused variables: trap_profiler_ptr_, go_
2022-12-23 Updated build to use rexjson library
2022-12-23 Updated Makefile
2022-12-24 Updated...
2022-12-24 Added MacOS usage example.
2022-12-28 Added support for capturing data
2023-01-02 Now using the newer version of rexjson++
2023-01-02 Updated .vscode files
2023-01-04 Clean up the velocity profiler code.
2023-01-05 The profiler now takes Vfin parameter.
2023-01-05 work in progress.
2023-01-05 save .vscode files
2023-01-05 Save experimental work
2023-01-06 Now using velocity in [ec/sec]
2023-01-09 Work on velocity profiler
2023-01-09 Updated STM32 libraries.
2023-01-13 Changed the type of the profiler input parameters to int64_t
2023-01-19 Added XY trajectory functions.
2023-01-19 Updated doc pages.
2023-05-06 Added schematics received from ZEC
2023-09-07 modified settings
2023-09-07 Added gitignore
2023-09-11 Fixed build warnings
2023-09-14 aded pos_offset property
2023-10-13 Added pos_offset
2023-10-14 Added util class sigmadrive/velocityprofiler/sigmadrive.py
2023-10-18 Revision 1 from ZEC.
2023-10-18 Added encoder_minas.h/cpp
2023-10-18 Increased the update_hz. Refactored the MotorDrive::EstimateRotor.
2023-10-19 Restored the calculation of E_ in EstimateRotor(). Changed the compiler optimization to O3
2023-10-19 Added the E_ calculation in EstimateRotor as commented out code for future reference.
2023-10-19 Added CdcIface::GetLine()
2023-10-19 Added RunTaskResetRotorAndHold()
2023-10-20 Added pole_offset_ parameter.
2023-10-21 Set the update_hz to 20000. Fixed pole_offset calibration.
2023-10-21 Changed UpdateRotor()
2023-10-22 added
2023-10-23 Modified c_cpp_properties.json file
2023-10-23 Changed the default tau_ration to 3
2023-10-25 Work on crash detection.
2023-10-25 Added crash_current and crash_backup props
2023-10-25 Implemented crash detection and related axes.
2023-11-01 Changed the update rate to 20000
2023-11-01 Added mvcirc and circpoints
2023-11-01 Disalbed crash detection
2023-11-01 Removed the default u.Go()
2023-12-01 Convert parameters to int
2024-04-25 Removed unused code for crash detection.
2024-04-25 Updated default PID coefficients.
2024-04-25 Updated launch.json with a new debug target.
2024-04-25 Added more code documentation.
2024-04-26 Updated pid_w_kp_
2024-05-05 Created simple CLP mode
2024-05-05 Added code comments
2024-05-10 Removed crash detection code.
2024-05-17 Added pulse chart
2024-05-17 Added clock_hz and mvrps, mvt RPC
2024-05-17 Changed optimization level to O2
2024-05-17 Removed rotor velocity filtration
2024-05-18 Fixed RPC calls.
2024-06-27 Work on pulse
2024-07-29 Fixed build errors
2024-08-11 Updated for STM32H743 device
2024-08-12 Updated ADC
2024-08-12 Updated ADC for H7
2024-09-18 Work on minas encoder reinitialization.
2024-09-18 Added method MotorDrive::InitializeEncoder()
